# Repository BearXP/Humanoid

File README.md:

# Humanoid
Along with Stefan di Donato, I am building a humanoid robot.

Controller: C.H.I.P running debian linux
Electronics: See PCBA folder
Mechanical: See https://cad.onshape.com/documents/673e2068db18134e20d03cef/w/27f3b55c71efa25a17beb110/e/45b7146fd14077735689123d

Enjoi :)

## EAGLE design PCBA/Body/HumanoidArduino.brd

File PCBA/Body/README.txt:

cd ~/Desktop
mkdir Eagle
cd Eagle
wget http://web.cadsoft.de/ftp/eagle/program/7.3/eagle-lin64-7.3.0.run

chmod a+x eagle-lin64-7.3.0.run
./eagle-lin64-7.3.0.run

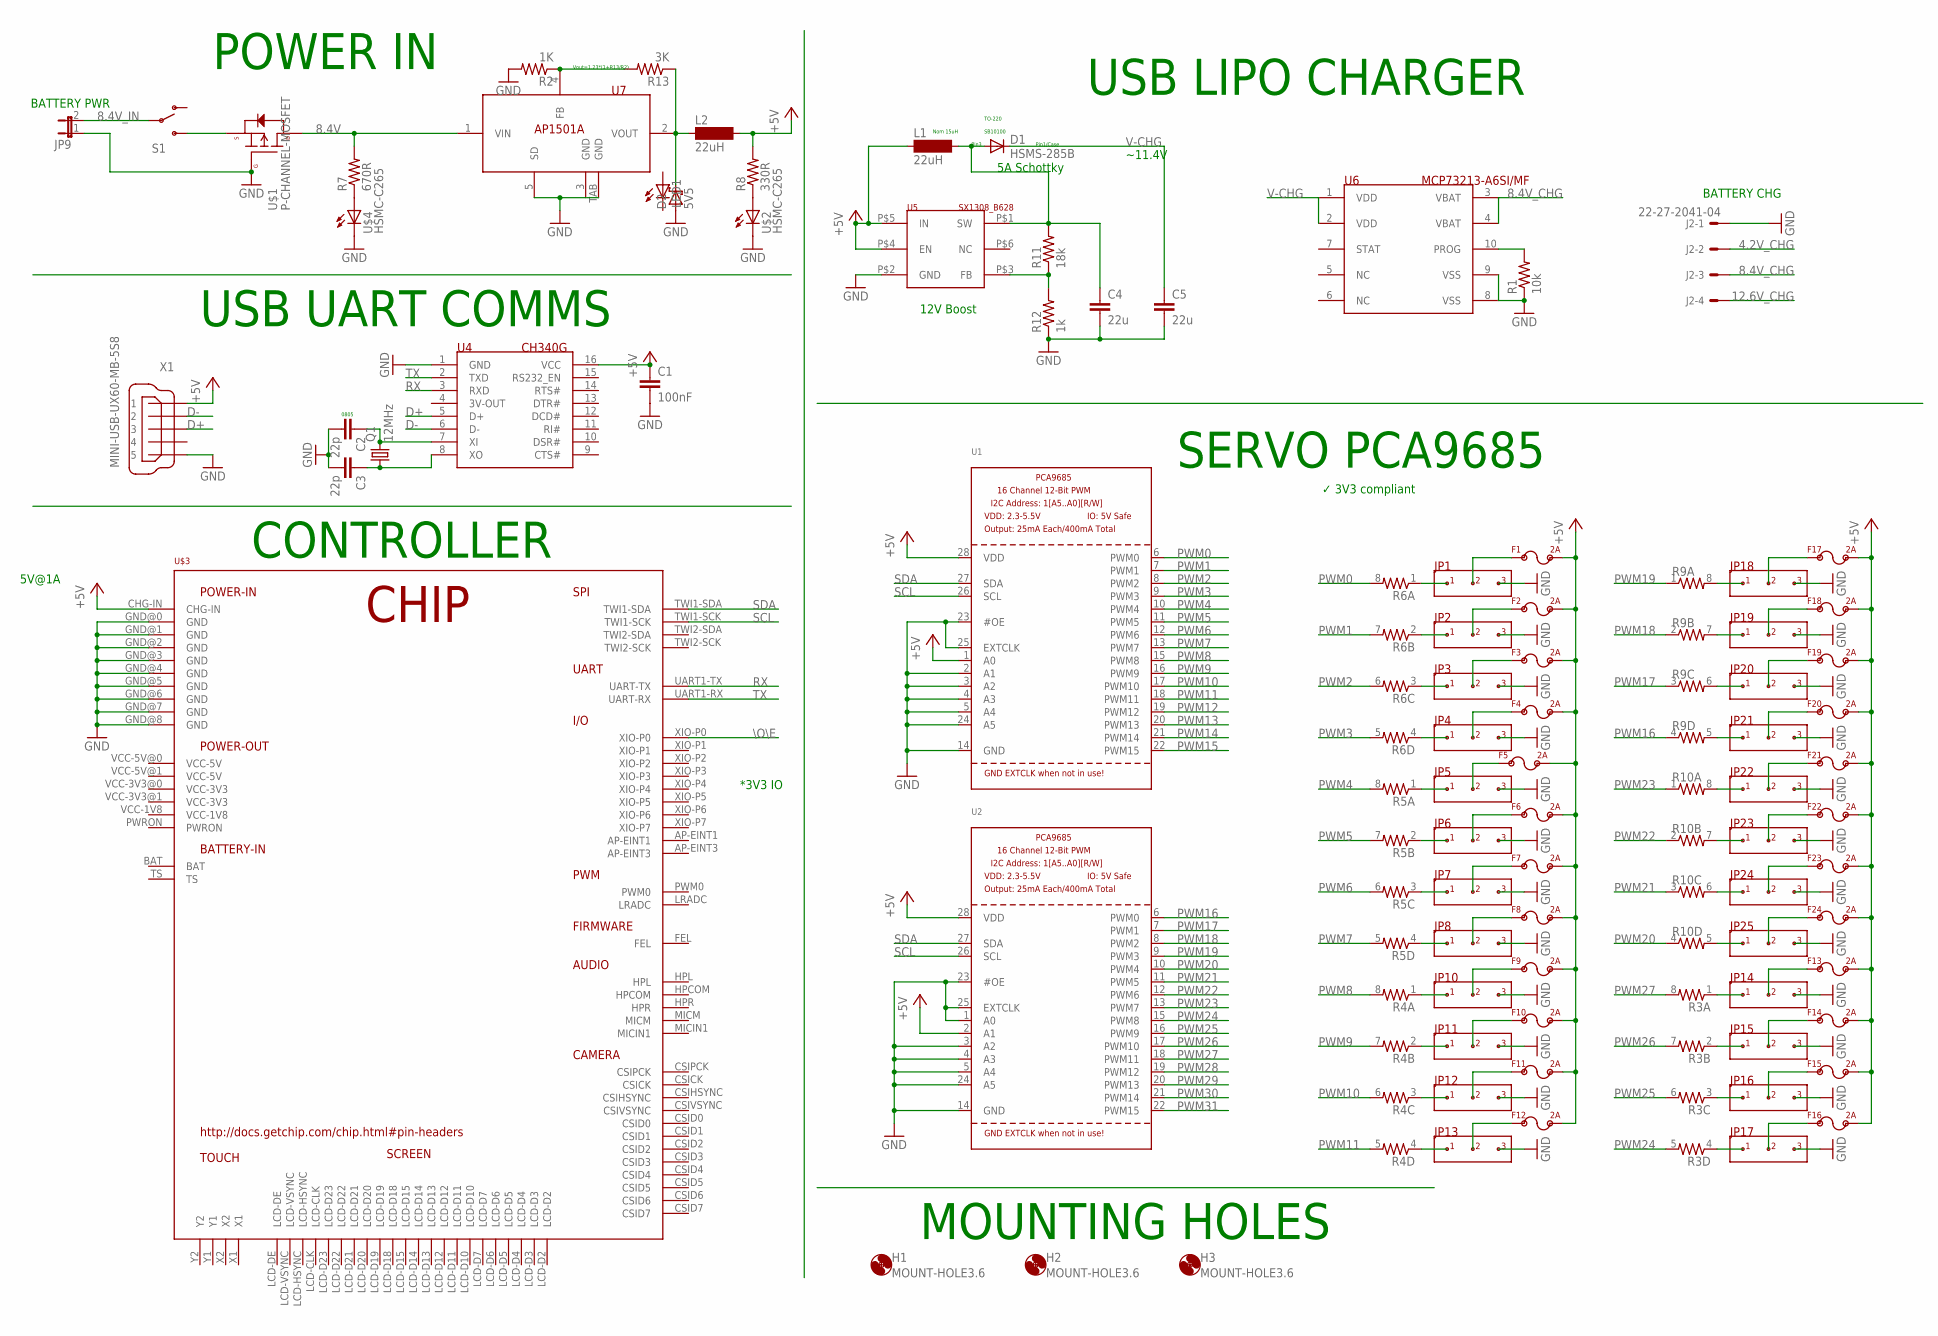
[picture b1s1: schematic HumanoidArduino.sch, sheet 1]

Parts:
C1: 100nF; C2.5-3
C2, C3: 22p; C2.5-3
C4, C5: 22u; C2.5-3
D1: HSMS-285B; SOT323
D2: 5V5; SOD323_ST
F1, F2, F3, F4, F5, F6, F7, F8, F9, F10, F11, F12, F13, F14, F15, F16, F17, F18, F19, F20, F21, F22, F23, F24: POLYSWITCH; 1206
H1, H2, H3: MOUNT-HOLE3.6; 3,6
J2: 22-27-2041-04; 6410-04
JP1, JP2, JP3, JP4, JP5, JP6, JP7, JP8, JP10, JP11, JP12, JP13, JP14, JP15, JP16, JP17, JP18, JP19, JP20, JP21, JP22, JP23, JP24, JP25: JUMPER_3X1_0.1; CONN_3X1_0.1"
JP9: JP1E; JP1
L1, L2: 22uH; MS85
LED1: LEDSML1206; SML1206
Q1: 12MHz; CSM-7X-DU
R1: 10k; 0805
R2: 1K; 0805
R3, R4, R5, R6, R9, R10: RESISTOR-ARRAY0603-ARV; 0603-ARV
R7: 670R; 0805
R8: 330R; 0805
R11: 18k; 0805
R12: 1k; 0805
R13: 3K; 0805
S1: SWITCH-SPDTPTH_LOCK; SWITCH-SPDT_LOCK.007S
U1, U2: PCA9685; TSSOP28
U4: CH340G; SO-16
U5: SX1308_B628; SOT23-6
U6: MCP73213-A6SI/MF; DFN300X300X100-11N
U7: AP1501A; TO-263-5
U$1: P-CHANNEL-MOSFET; SOT23-3
U$2, U$4: HSMC-C265
U$3: CHIP
X1: MINI-USB-UX60-MB-5S8; UX60-MB-5S8

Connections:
4.2V_CHG: J2.2
8.4V: R7.2, U7.1 (VIN), U$1.3 (D)
8.4V_CHG: J2.3
8.4V_IN: JP9.2, S1.2
12.6V_CHG: J2.4
+5V: C1.1, F1.P$2, F2.P$2, F3.P$2, F4.P$2, F5.P$2, F6.P$2, F7.P$2, F8.P$2, F9.P$2, F10.P$2, F11.P$2, F12.P$2, F13.P$2, F14.P$2, F15.P$2, F16.P$2, F17.P$2, F18.P$2, F19.P$2, F20.P$2, F21.P$2, F22.P$2, F23.P$2, F24.P$2, L2.2, R8.2, U1.1 (A0), U1.28 (VDD), U2.2 (A1), U2.28 (VDD), U4.16 (VCC), U$3.CHG-IN, X1.1
D+: U4.5 (D+), X1.3
D-: U4.6 (D-), X1.2
GND: C1.2, C2.2, C3.2, C4.2, C5.2, D2.A, J2.1, JP1.P$3 (3), JP2.P$3 (3), JP3.P$3 (3), JP4.P$3 (3), JP5.P$3 (3), JP6.P$3 (3), JP7.P$3 (3), JP8.P$3 (3), JP9.1, JP10.P$3 (3), JP11.P$3 (3), JP12.P$3 (3), JP13.P$3 (3), JP14.P$3 (3), JP15.P$3 (3), JP16.P$3 (3), JP17.P$3 (3), JP18.P$3 (3), JP19.P$3 (3), JP20.P$3 (3), JP21.P$3 (3), JP22.P$3 (3), JP23.P$3 (3), JP24.P$3 (3), JP25.P$3 (3), R1.1, R2.2, R12.1, U1.2 (A1), U1.3 (A2), U1.4 (A3), U1.5 (A4), U1.14 (GND), U1.23 (#OE), U1.24 (A5), U1.25 (EXTCLK), U2.1 (A0), U2.3 (A2), U2.4 (A3), U2.5 (A4), U2.14 (GND), U2.23 (#OE), U2.24 (A5), U2.25 (EXTCLK), U4.1 (GND), U5.P$2 (GND), U6.9 (VSS), U7.5 (SD), U7.TAB (GND), U$1.1 (G), U$2.C, U$3.GND@0 (GND), U$3.GND@1 (GND), U$3.GND@2 (GND), U$3.GND@3 (GND), U$3.GND@4 (GND), U$3.GND@5 (GND), U$3.GND@6 (GND), U$3.GND@7 (GND), U$3.GND@8 (GND), U$4.C, X1.5
unnamed: JP1.P$1 (1), R6.1
unnamed: JP2.P$1 (1), R6.2 (1)
unnamed: JP3.P$1 (1), R6.3 (1)
unnamed: JP4.P$1 (1), R6.4 (1)
unnamed: F3.P$1, JP3.P$2 (2)
unnamed: F4.P$1, JP4.P$2 (2)
unnamed: F16.P$1, JP17.P$2 (2)
unnamed: F15.P$1, JP16.P$2 (2)
unnamed: F14.P$1, JP15.P$2 (2)
unnamed: F13.P$1, JP14.P$2 (2)
unnamed: F12.P$1, JP13.P$2 (2)
unnamed: F11.P$1, JP12.P$2 (2)
unnamed: F10.P$1, JP11.P$2 (2)
unnamed: F9.P$1, JP10.P$2 (2)
unnamed: F8.P$1, JP8.P$2 (2)
unnamed: F7.P$1, JP7.P$2 (2)
unnamed: F6.P$1, JP6.P$2 (2)
unnamed: F5.P$1, JP5.P$2 (2)
unnamed: JP5.P$1 (1), R5.1
unnamed: JP6.P$1 (1), R5.2 (1)
unnamed: JP7.P$1 (1), R5.3 (1)
unnamed: JP8.P$1 (1), R5.4 (1)
unnamed: JP10.P$1 (1), R4.1
unnamed: JP11.P$1 (1), R4.2 (1)
unnamed: S1.3 (S), U$1.2 (S)
unnamed: F1.P$1, JP1.P$2 (2)
unnamed: R7.1, U$4.A
unnamed: R8.1, U$2.A
unnamed: F2.P$1, JP2.P$2 (2)
unnamed: JP12.P$1 (1), R4.3 (1)
unnamed: JP13.P$1 (1), R4.4 (1)
unnamed: JP14.P$1 (1), R3.1
unnamed: JP15.P$1 (1), R3.2 (1)
unnamed: JP16.P$1 (1), R3.3 (1)
unnamed: JP17.P$1 (1), R3.4 (1)
unnamed: F21.P$1, JP22.P$2 (2)
unnamed: F20.P$1, JP21.P$2 (2)
unnamed: F19.P$1, JP20.P$2 (2)
unnamed: F18.P$1, JP19.P$2 (2)
unnamed: F17.P$1, JP18.P$2 (2)
unnamed: JP18.P$1 (1), R9.8 (2)
unnamed: JP19.P$1 (1), R9.7 (2)
unnamed: JP20.P$1 (1), R9.6 (2)
unnamed: JP21.P$1 (1), R9.5 (2)
unnamed: JP22.P$1 (1), R10.8 (2)
unnamed: F22.P$1, JP23.P$2 (2)
unnamed: F23.P$1, JP24.P$2 (2)
unnamed: F24.P$1, JP25.P$2 (2)
unnamed: JP23.P$1 (1), R10.7 (2)
unnamed: JP24.P$1 (1), R10.6 (2)
unnamed: JP25.P$1 (1), R10.5 (2)
unnamed: C2.1, Q1.2, U4.7 (XI)
unnamed: C3.1, Q1.1, U4.8 (XO)
unnamed: L1.1, U5.P$4 (EN), U5.P$5 (IN)
unnamed: R11.1, R12.2, U5.P$3 (FB)
unnamed: C4.1, D1.1 (A), L1.2, R11.2, U5.P$1 (SW)
unnamed: R1.2, U6.10 (PROG)
unnamed: R2.1, R13.2, U7.4 (FB)
unnamed: D2.C, L2.1, R13.1, U7.2 (VOUT)
PWM0: R6.8 (2), U1.6 (PWM0)
PWM1: R6.7 (2), U1.7 (PWM1)
PWM2: R6.6 (2), U1.8 (PWM2)
PWM3: R6.5 (2), U1.9 (PWM3)
PWM4: R5.8 (2), U1.10 (PWM4)
PWM5: R5.7 (2), U1.11 (PWM5)
PWM6: R5.6 (2), U1.12 (PWM6)
PWM7: R5.5 (2), U1.13 (PWM7)
PWM8: R4.8 (2), U1.15 (PWM8)
PWM9: R4.7 (2), U1.16 (PWM9)
PWM10: R4.6 (2), U1.17 (PWM10)
PWM11: R4.5 (2), U1.18 (PWM11)
PWM12: U1.19 (PWM12)
PWM13: U1.20 (PWM13)
PWM14: U1.21 (PWM14)
PWM15: U1.22 (PWM15)
PWM16: R9.4 (1), U2.6 (PWM0)
PWM17: R9.3 (1), U2.7 (PWM1)
PWM18: R9.2 (1), U2.8 (PWM2)
PWM19: R9.1, U2.9 (PWM3)
PWM20: R10.4 (1), U2.10 (PWM4)
PWM21: R10.3 (1), U2.11 (PWM5)
PWM22: R10.2 (1), U2.12 (PWM6)
PWM23: R10.1, U2.13 (PWM7)
PWM24: R3.5 (2), U2.15 (PWM8)
PWM25: R3.6 (2), U2.16 (PWM9)
PWM26: R3.7 (2), U2.17 (PWM10)
PWM27: R3.8 (2), U2.18 (PWM11)
PWM28: U2.19 (PWM12)
PWM29: U2.20 (PWM13)
PWM30: U2.21 (PWM14)
PWM31: U2.22 (PWM15)
RX: U4.3 (RXD), U$3.UART1-TX (UART-TX)
SCL: U1.26 (SCL), U2.26 (SCL), U$3.TWI1-SCK
SDA: U1.27 (SDA), U2.27 (SDA), U$3.TWI1-SDA
TX: U4.2 (TXD), U$3.UART1-RX (UART-RX)
V-CHG: C5.1, D1.3 (C)
\O\E: U$3.XIO-P0

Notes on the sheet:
BATTERY CHG
SERVO PCA9685
POWER IN
CONTROLLER
*3V3 IO
￼ ✓ 3V3 compliant
5V@1A
BATTERY PWR
MOUNTING HOLES
USB UART COMMS
USB LIPO CHARGER
12V Boost
~11.4V
5A Schottky
Vout=1.23*(1+R13/R2)
0805
Nom 15uH
SB10100
TO-220
Pin3
Pin1/Case

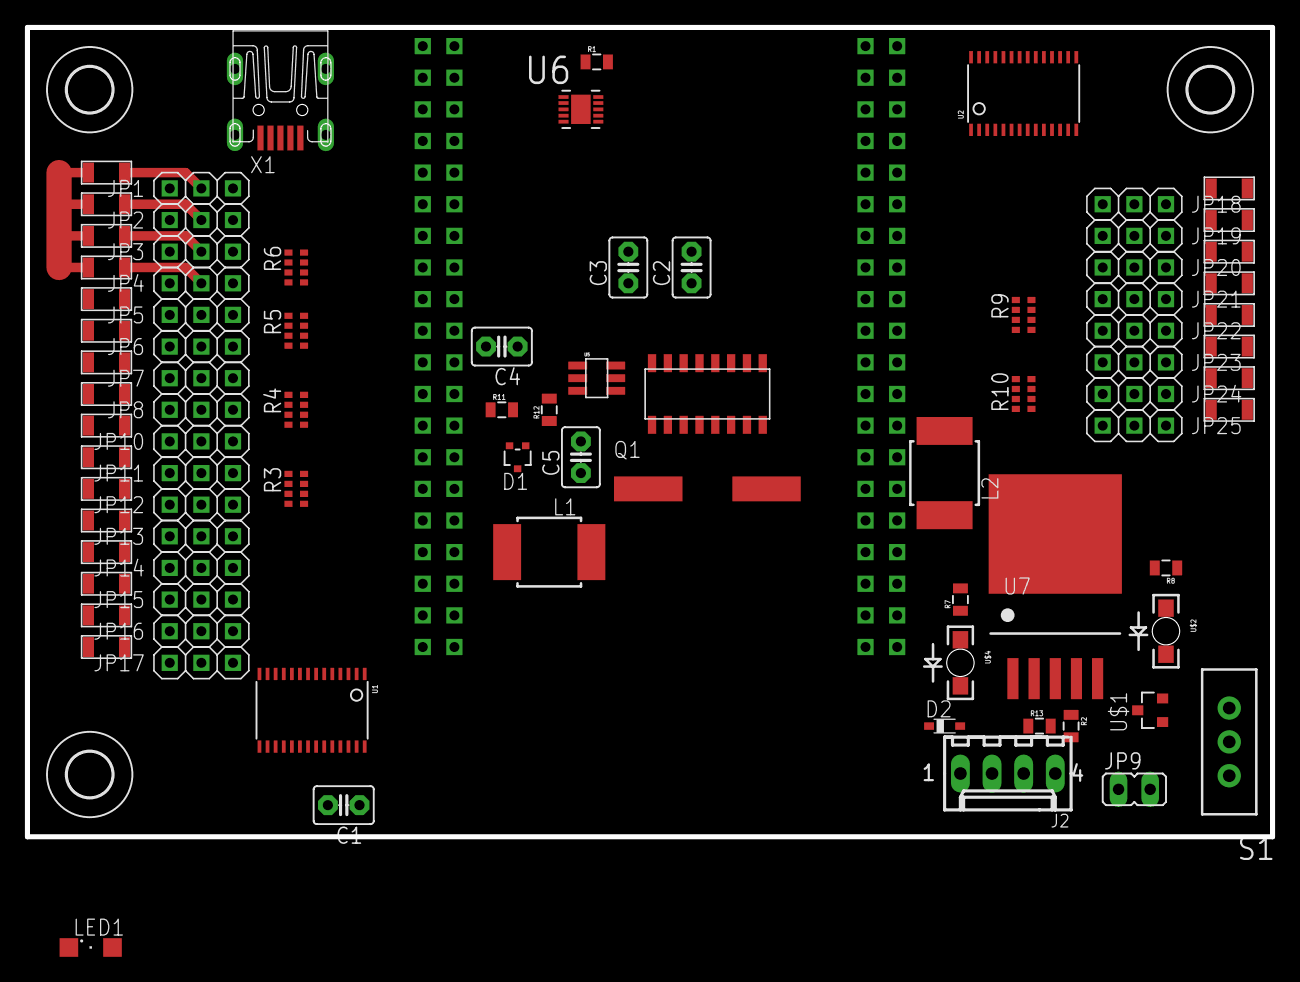
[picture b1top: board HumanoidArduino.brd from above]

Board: 2 copper layers, 100.0 x 65.0 mm, 89 parts (1 on the bottom side), 94 nets.

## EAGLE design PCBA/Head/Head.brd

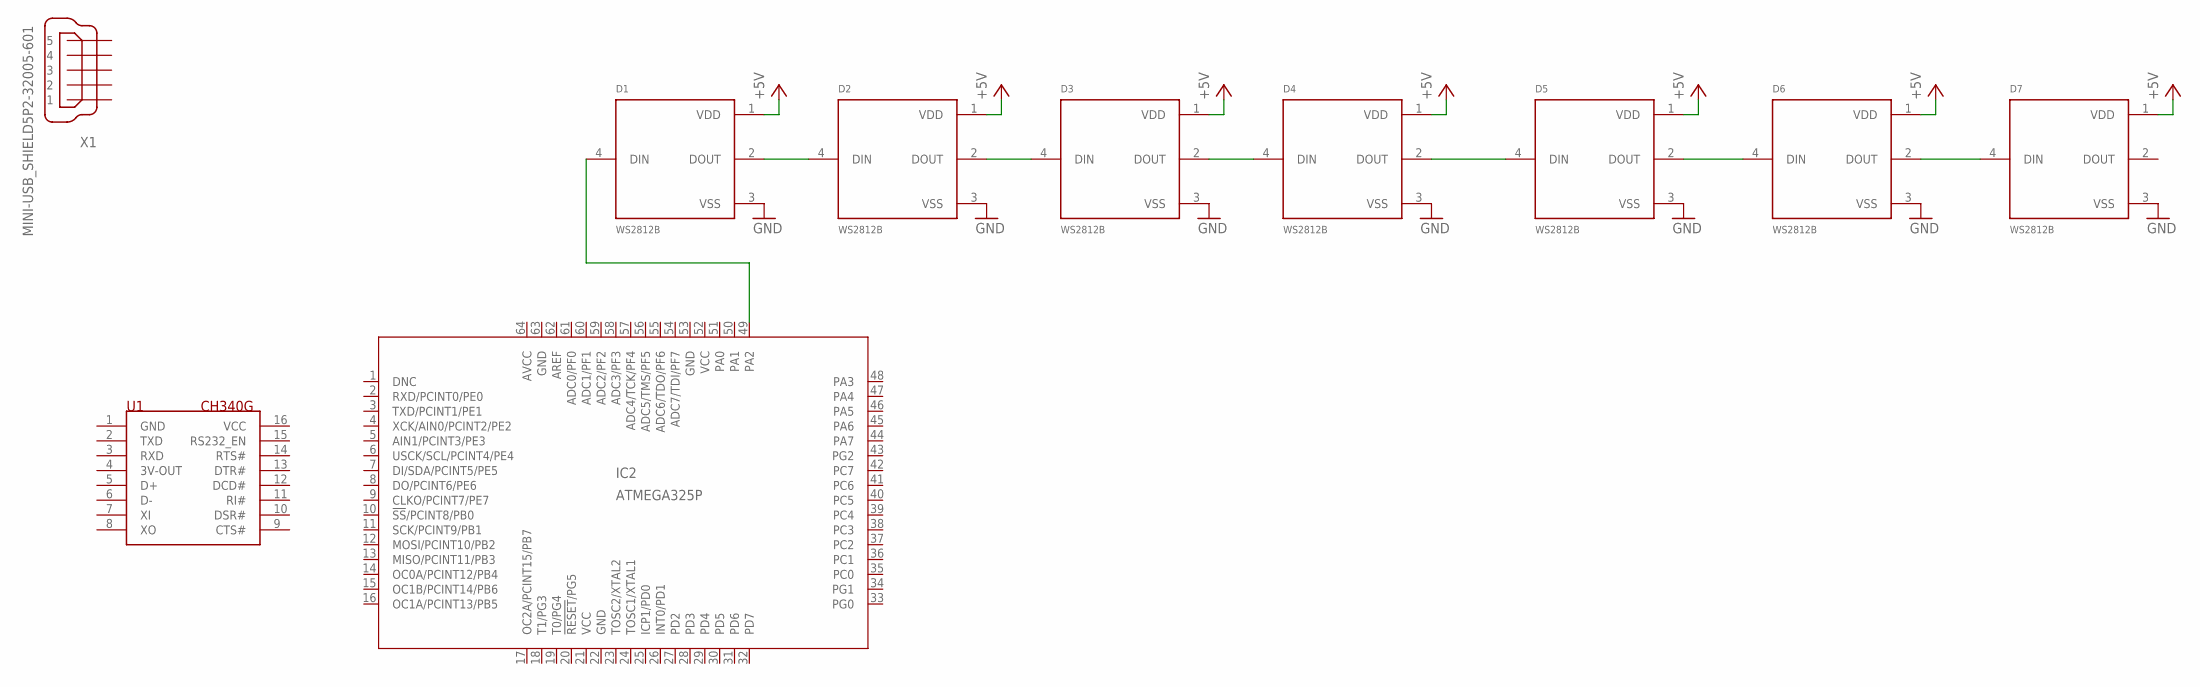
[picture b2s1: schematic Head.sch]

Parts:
D1, D2, D3, D4, D5, D6, D7: WS2812B; LED_WS2812B
IC2: ATMEGA325P; 64M1
U1: CH340G; SO-16
X1: MINI-USB_SHIELD5P2-32005-601; 32005-601

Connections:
0V: D1.3 (VSS), D2.3 (VSS), D3.3 (VSS), D4.3 (VSS), D5.3 (VSS), D6.3 (VSS), D7.3 (VSS)
AVCC: IC2.64 (AVCC)
GND: IC2.22 (GND), IC2.53 (GND), IC2.63 (GND)
unnamed: D1.2 (DOUT), D2.4 (DIN)
unnamed: D2.2 (DOUT), D3.4 (DIN)
unnamed: D3.2 (DOUT), D4.4 (DIN)
unnamed: D4.2 (DOUT), D5.4 (DIN)
unnamed: D5.2 (DOUT), D6.4 (DIN)
unnamed: D6.2 (DOUT), D7.4 (DIN)
unnamed: D1.4 (DIN), IC2.49 (PA2)
VCC: D1.1 (VDD), D2.1 (VDD), D3.1 (VDD), D4.1 (VDD), D5.1 (VDD), D6.1 (VDD), D7.1 (VDD), IC2.21 (VCC), IC2.52 (VCC)

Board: 2 copper layers, 10 parts (0 on the bottom side), 10 nets, no tracks yet.

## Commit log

2016-11-18 Initial release
2016-11-19 Replaces Arduino w. CHIP
2016-11-23 GPIO working!
2016-11-23 Testing I2C
2016-11-29 Fixed python issues
2016-11-29 Aligning frequency & pwm values with arduino PWM test. looked through Adafruit_PWMServoDriver.cpp and pwmtest to ensure values are logical
2016-11-30 testing new servo wave pattern
2016-11-30 added printouts
2016-11-30 testing web server to control servos
2016-11-30 added robot picture
2016-11-30 slowed down servo speed
2016-12-01 fixed bug
2016-12-01 Restructured. Robot image loads correctly.
2016-12-01 Testing adafruit's PCA9685 library
2016-12-01 i2c workinggit add .! servo does nice wave function
2016-12-01 increased range to ~180degrees
2016-12-01 website uses tabs now xx
2016-12-02 Flask is working - all hardcoded values though
2016-12-02 satrted moving html to variables
2016-12-02 Webserver is working xo
2016-12-02 initial main code
2016-12-02 added drivers to main
2016-12-02 testing pwm_val
2016-12-02 Main working x
2016-12-02 Added print of IP address
2016-12-06 Started using aliexpress parts for PCBA
2016-12-06 Started making setup.sh for getting the code to work
2016-12-06 Playimg around with a sqlite db to mamage patterns
2016-12-08 Working on PCBA
2016-12-08 Continued work on PCBA
2016-12-12 more PCBA work
2016-12-13 Working on PCB
2016-12-13 Add overview
2016-12-13 gitignore
2016-12-13 Added boost circuit for charging
2016-12-14 started on the head PCBA
2016-12-15 PCBA again
2016-12-15 Added frame to head PCBA
    Make it look gewd.
2016-12-16 Added ngrok
2016-12-16 testing git
2016-12-17 started working with templates
2016-12-17 working on config page
2016-12-18 Moved config to SQLite3 Database. Python code/web pages are broken now
2016-12-19 html shows .db data, started code to twrite back to db'
2016-12-19 Writing back to DB
2016-12-19 Config working. Started working on Pose
2016-12-19 Using proper 5V buck reg
2016-12-20 selected a few more parts for the PCB
2016-12-21 Code: Poses working better. Config broken
2016-12-22 working on config/poses
2016-12-25 workimg on poses
2016-12-26 commit on branch B
2016-12-26 Pose updated - needs testing - should move to pose/save correctly. Need to figure out the whole 'not refreshing thing' its got going on at the moment
2016-12-27 working on addimg new poses
2016-12-27 Pose working. Can make prettier though
2016-12-27 started walk sequence
2016-12-27 Seq. page showing delay times
2016-12-29 Turned autocomplete off, and further tweaks to getet the drop down menus working. Theyre working fine now :). Started SaveDb for Sequences
2016-12-30 Save and execute sequences now works :)
2016-12-30 fixed a bug where the drop down on the pose screen wouldnt change the display correctly. fixed a bug where the latest pose/sequence wouldnt display on page load due to the difference between row# and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
2017-01-02 working on save as sequence
2017-01-03 Save as new sequence and delete sequence working
2017-01-14 Legs working
2017-01-14 Testing walk animation
2017-01-14 Animation half donegit add .
2017-01-30 stole miguel grinbergs webcam streaming
2017-01-30 takes pictures!
2017-01-30 Video streaming working on the CHIP
2017-01-30 Video streaming working on the CHIPgit add .
2017-01-30 testing 2 cameras
2017-01-30 Testing dual cameras
2017-01-31 Testing using VLC for streaming video
2017-02-09 increased range of config
2017-02-12 Fixed issue where config didn't save properly
2017-02-12 Fixed bug - Coulsn't move
2017-02-21 Testing Sockets. Added multiple test setups
2017-02-21 Fixed spacing issue which caused the config page to not render
2017-02-27 Websockets still not working :(
2017-03-01 Asynchronous messaging working! Now to break it :)
2017-03-02 Echogit add .
2017-03-02 Passing multiple dict values
2017-03-03 Config workinggit add .!
2017-03-06 fixed bug with move_servo

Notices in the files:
parts and their libraries:
SparkFun-Resistors: Licensing: Creative Commons ShareAlike 4.0 International - https://creativecommons.org/licenses/by-sa/4.0
